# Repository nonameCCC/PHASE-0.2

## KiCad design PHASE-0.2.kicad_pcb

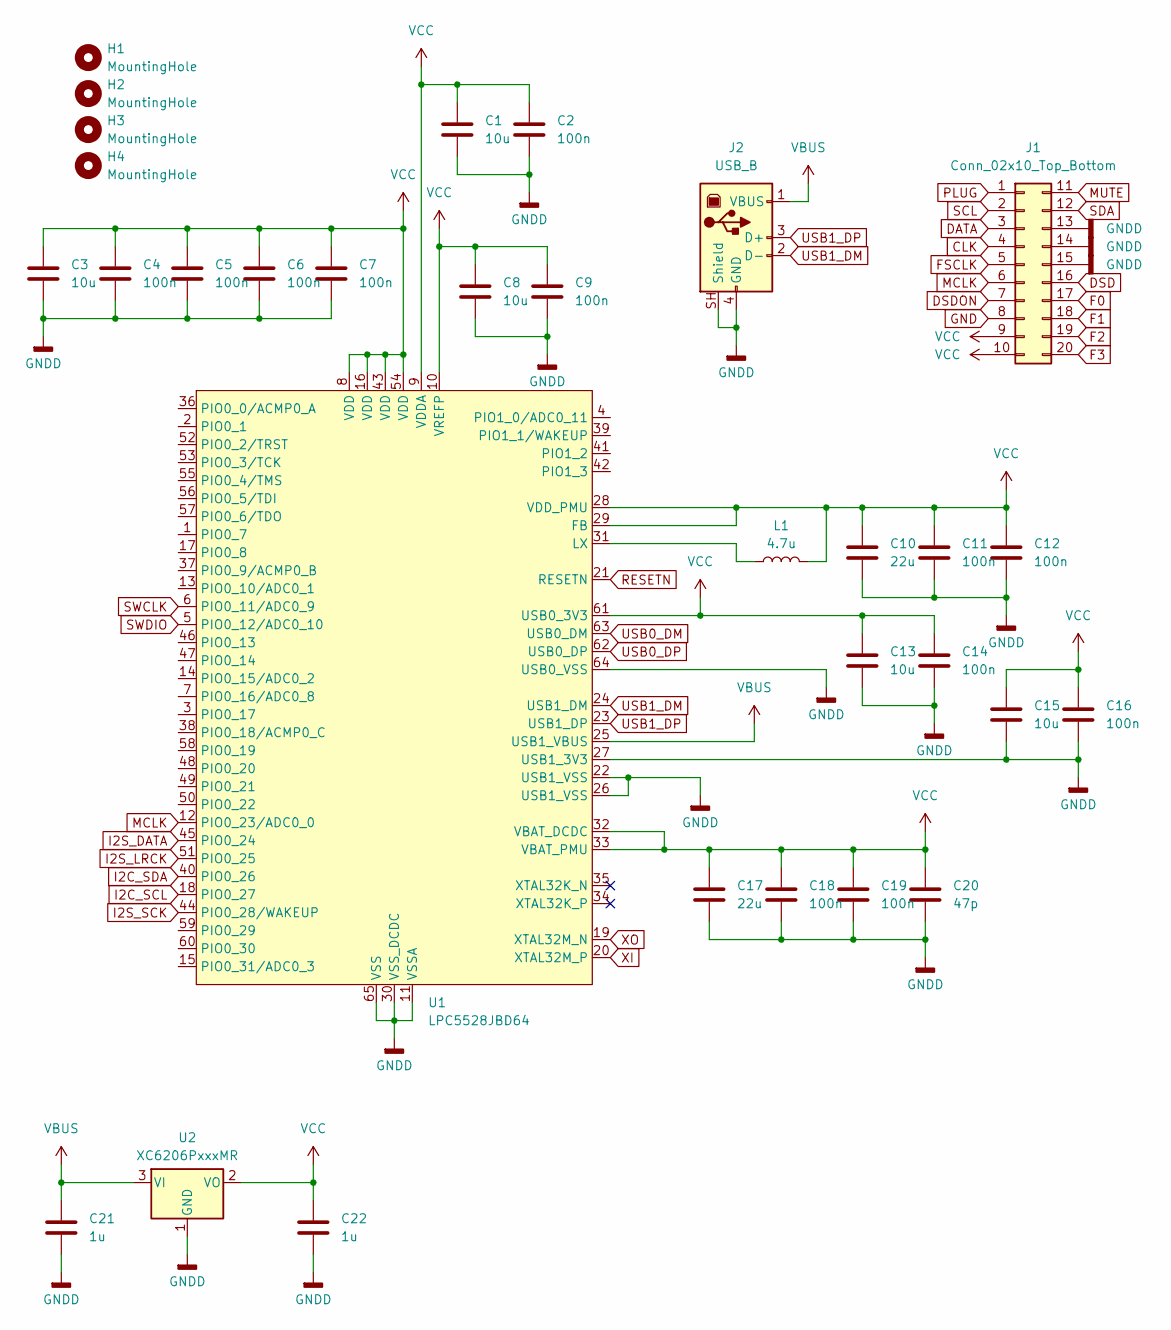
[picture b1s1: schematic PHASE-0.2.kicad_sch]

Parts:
C1, C3, C8, C13, C15: 10u; C_0603_1608Metric
C2, C4, C5, C6, C7, C9, C11, C12, C14, C16, C18, C19: 100n; C_0402_1005Metric
C10, C17: 22u; C_0603_1608Metric
C20: 47p; C_0402_1005Metric
C21, C22: 1u; C_0402_1005Metric
H1, H2, H3, H4: MountingHole; MountingHole_2.2mm_M2
J1: Conn_02x10_Top_Bottom; PinHeader_2x10_P2.54mm_Vertical
J2: USB_B; USB_B_Lumberg_2411_02_Horizontal
L1: 4.7u; L_Murata_DFE201610P
U1: LPC5528JBD64; TQFP-64-1EP_10x10mm_P0.5mm_EP3.6x3.6mm
U2: XC6206PxxxMR; SOT-23-3

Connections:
CLK: J1.4
DATA: J1.3
DSD: J1.16
DSDON: J1.7
F0: J1.17
F1: J1.18
F2: J1.19
F3: J1.20
FSCLK: J1.5
GND: J1.8
GNDD: C1.2, C2.2, C3.2, C4.2, C5.2, C6.2, C7.2, C8.2, C9.2, C10.2, C11.2, C12.2, C13.2, C14.2, C15.2, C16.2, C17.2, C18.2, C19.2, C20.2, C21.2, C22.2, J1.13, J1.14, J1.15, J2.4 (GND), J2.SH (Shield), U1.11 (VSSA), U1.22 (USB1_VSS), U1.26 (USB1_VSS), U1.27 (USB1_3V3), U1.30 (VSS_DCDC), U1.64 (USB0_VSS), U1.65 (VSS), U2.1 (GND)
I2C_SCL: U1.18 (PIO0_27)
I2C_SDA: U1.40 (PIO0_26)
I2S_DATA: U1.45 (PIO0_24)
I2S_LRCK: U1.51 (PIO0_25)
I2S_SCK: U1.44 (PIO0_28/WAKEUP)
MCLK: J1.6, U1.12 (PIO0_23/ADC0_0)
MUTE: J1.11
unnamed: L1.1, U1.31 (LX)
PLUG: J1.1
RESETN: U1.21 (RESETN)
SCL: J1.2
SDA: J1.12
SWCLK: U1.6 (PIO0_11/ADC0_9)
SWDIO: U1.5 (PIO0_12/ADC0_10)
USB0_DM: U1.63 (USB0_DM)
USB0_DP: U1.62 (USB0_DP)
USB1_DM: J2.2 (D-), U1.24 (USB1_DM)
USB1_DP: J2.3 (D+), U1.23 (USB1_DP)
VBUS: C21.1, J2.1 (VBUS), U1.25 (USB1_VBUS), U2.3 (VI)
VCC: C1.1, C2.1, C3.1, C4.1, C5.1, C6.1, C7.1, C8.1, C9.1, C10.1, C11.1, C12.1, C13.1, C14.1, C15.1, C16.1, C17.1, C18.1, C19.1, C20.1, C22.1, J1.9, J1.10, L1.2, U1.8 (VDD), U1.9 (VDDA), U1.10 (VREFP), U1.16 (VDD), U1.28 (VDD_PMU), U1.29 (FB), U1.32 (VBAT_DCDC), U1.33 (VBAT_PMU), U1.43 (VDD), U1.54 (VDD), U1.61 (USB0_3V3), U2.2 (VO)
XI: U1.20 (XTAL32M_P)
XO: U1.19 (XTAL32M_N)

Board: 2 copper layers, 31 parts (0 on the bottom side), 7 nets, no tracks yet.

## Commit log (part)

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2025-10-13 Copy Gitignore to Subfolders
2025-10-13 Create New KiCad Projects
2025-10-16 Add Symbols of FPGA and MCU
